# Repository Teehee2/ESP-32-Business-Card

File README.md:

# ESP-32-Business-Card
Personal Business Card with fully functional ESP-32 and NFC

Latest version V0.2

Friends with version V0.1: PLEASE TAKE NOTE!
DO NOT USE CLIP POINT USB 5V! IT WILL SHORT TO GROUND!

For DIY users:
V0.1 is flawed with mixed up tx/rx traces! Enamel wires need to be flown to use ESP32!
SW1 does not work with resistor R9, it is recommended to short the pads across R9.

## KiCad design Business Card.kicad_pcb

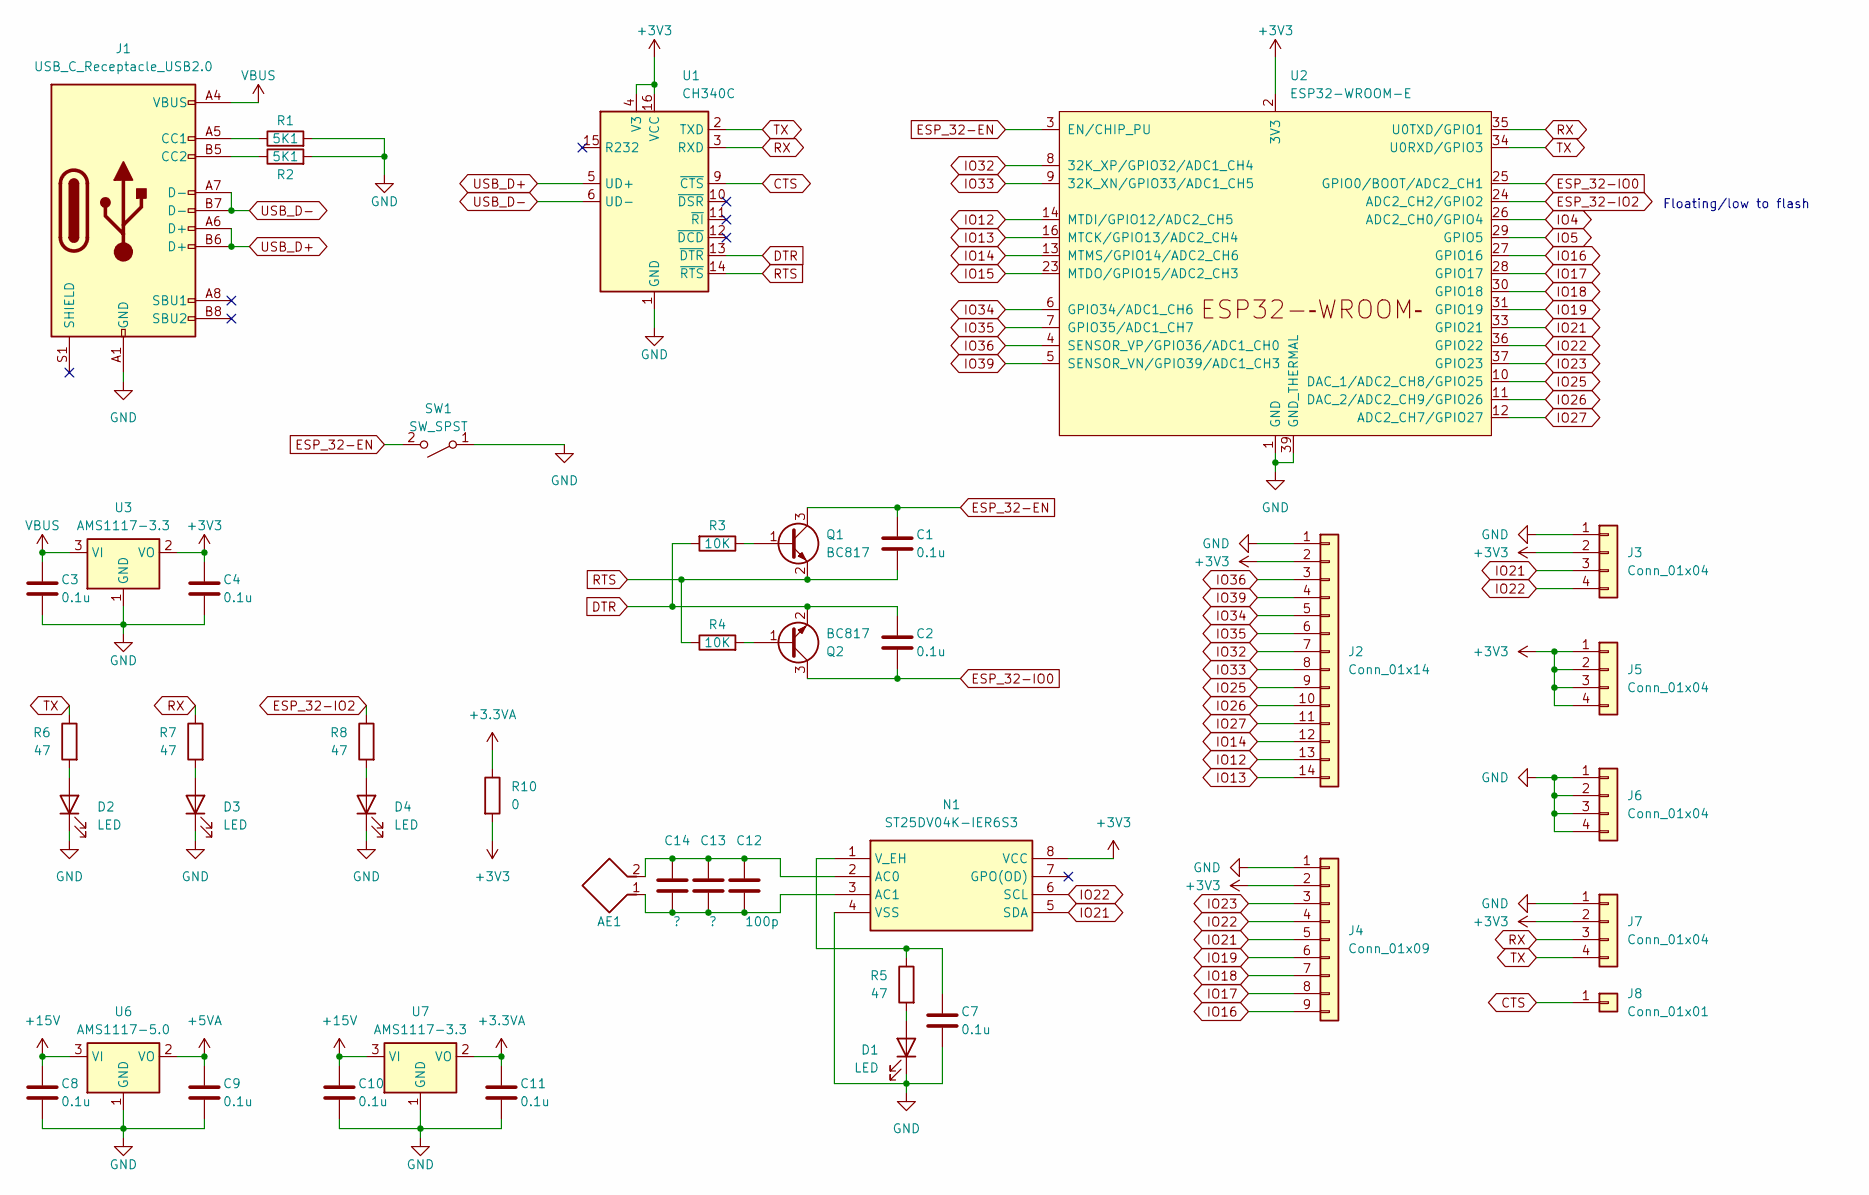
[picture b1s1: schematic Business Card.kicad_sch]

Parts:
AE1: NFC2
C1, C2, C3, C4, C7, C8, C9, C10, C11: 0.1u; C_0603_1608Metric
C12: 100p; C_0603_1608Metric
C13, C14: ?; C_0603_1608Metric
D1, D2, D3, D4: LED; LED_0603_1608Metric
J1: USB_C_Receptacle_USB2.0; USB_C_Receptacle_HRO_TYPE-C-31-M-12
J2: Conn_01x14; PinHeader_1x14_P2.54mm_Vertical_1_No_Silk
J3, J5, J6, J7: Conn_01x04; PinHeader_1x04_P2.54mm_Vertical_No_Silk
J4: Conn_01x09; PinHeader_1x09_P2.54mm_Vertical_No_Silk
J8: Conn_01x01; PinHeader_1x01_P2.54mm_Vertical_No_Silk
N1: ST25DV04K-IER6S3; SOIC-8-1EP_3.9x4.9mm_P1.27mm_EP2.41x3.3mm; Manufacturer_Part_Number ST25DV04K-IER6S3; Mouser Part Number 511-ST25DV04K-IER6S3
Q1, Q2: BC817; SOT-23
R1, R2: 5K1; R_0603_1608Metric
R3, R4: 10K; R_0603_1608Metric
R5, R6, R7, R8: 47; R_0603_1608Metric
R10: 0; R_0603_1608Metric
SW1: SW_SPST; SW_DIP_SPSTx01_Slide_Copal_CHS-01B_W7.62mm_P1.27mm
U1: CH340C; SOIC-16_3.9x9.9mm_P1.27mm
U2: ESP32-WROOM-E; ESP32-WROOM-32E
U3, U7: AMS1117-3.3; SOT-223-3_TabPin2
U6: AMS1117-5.0; SOT-223-3_TabPin2

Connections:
+3.3VA: C11.1, R10.1, U7.2 (VO)
+3V3: C4.1, J2.2, J3.2, J4.2, J5.1, J5.2, J5.3, J5.4, J7.2, N1.8 (VCC), R10.2, U1.4 (V3), U1.16 (VCC), U2.2 (3V3), U3.2 (VO)
+5VA: C9.1, U6.2 (VO)
+15V: C8.1, C10.1, U6.3 (VI), U7.3 (VI)
CTS: J8.1, U1.9 (~CTS)
DTR: C2.1, Q2.2 (E), R3.2, U1.13 (~DTR)
ESP_32-EN: C1.1, Q1.3 (C), SW1.2 (B), U2.3 (EN/CHIP_PU)
ESP_32-IO0: C2.2, Q2.3 (C), U2.25 (GPIO0/BOOT/ADC2_CH1)
ESP_32-IO2: R8.1, U2.24 (ADC2_CH2/GPIO2)
GND: C3.2, C4.2, C7.2, C8.2, C9.2, C10.2, C11.2, D1.1 (K), D2.1 (K), D3.1 (K), D4.1 (K), J1.A1 (GND), J1.A12 (GND), J1.B1 (GND), J1.B12 (GND), J2.1, J3.1, J4.1, J6.1, J6.2, J6.3, J6.4, J7.1, N1.4 (VSS), R1.2, R2.2, SW1.1 (A), U1.1 (GND), U2.1 (GND), U2.15 (GND), U2.38 (GND), U2.39 (GND_THERMAL), U3.1 (GND), U6.1 (GND), U7.1 (GND); also elsewhere on the board
IO4: U2.26 (ADC2_CH0/GPIO4)
IO5: U2.29 (GPIO5)
IO12: J2.13, U2.14 (MTDI/GPIO12/ADC2_CH5)
IO13: J2.14, U2.16 (MTCK/GPIO13/ADC2_CH4)
IO14: J2.12, U2.13 (MTMS/GPIO14/ADC2_CH6)
IO15: U2.23 (MTDO/GPIO15/ADC2_CH3)
IO16: J4.9, U2.27 (GPIO16)
IO17: J4.8, U2.28 (GPIO17)
IO18: J4.7, U2.30 (GPIO18)
IO19: J4.6, U2.31 (GPIO19)
IO21: J3.3, J4.5, N1.5 (SDA), U2.33 (GPIO21)
IO22: J3.4, J4.4, N1.6 (SCL), U2.36 (GPIO22)
IO23: J4.3, U2.37 (GPIO23)
IO25: J2.9, U2.10 (DAC_1/ADC2_CH8/GPIO25)
IO26: J2.10, U2.11 (DAC_2/ADC2_CH9/GPIO26)
IO27: J2.11, U2.12 (ADC2_CH7/GPIO27)
IO32: J2.7, U2.8 (32K_XP/GPIO32/ADC1_CH4)
IO33: J2.8, U2.9 (32K_XN/GPIO33/ADC1_CH5)
IO34: J2.5, U2.6 (GPIO34/ADC1_CH6)
IO35: J2.6, U2.7 (GPIO35/ADC1_CH7)
IO36: J2.3, U2.4 (SENSOR_VP/GPIO36/ADC1_CH0)
IO39: J2.4, U2.5 (SENSOR_VN/GPIO39/ADC1_CH3)
unnamed: D1.2 (A), R5.2
unnamed: D2.2 (A), R6.2
unnamed: D3.2 (A), R7.2
unnamed: D4.2 (A), R8.2
unnamed: J1.A5 (CC1), R1.1
unnamed: J1.B5 (CC2), R2.1
unnamed: AE1.2, C12.1, C13.1, C14.1, N1.2 (AC0)
unnamed: AE1.1, C12.2, C13.2, C14.2, N1.3 (AC1)
unnamed: C7.1, N1.1 (V_EH), R5.1
unnamed: Q1.1 (B), R3.1
unnamed: Q2.1 (B), R4.2
RTS: C1.2, Q1.2 (E), R4.1, U1.14 (~RTS)
RX: J7.3, R7.1, U1.3 (RXD), U2.35 (U0TXD/GPIO1)
TX: J7.4, R6.1, U1.2 (TXD), U2.34 (U0RXD/GPIO3)
USB_D+: J1.A6 (D+), J1.B6 (D+), U1.5 (UD+)
USB_D-: J1.A7 (D-), J1.B7 (D-), U1.6 (UD-)
VBUS: C3.1, J1.A4 (VBUS), J1.A9 (VBUS), J1.B4 (VBUS), J1.B9 (VBUS), U3.3 (VI)

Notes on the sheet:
Floating/low to flash

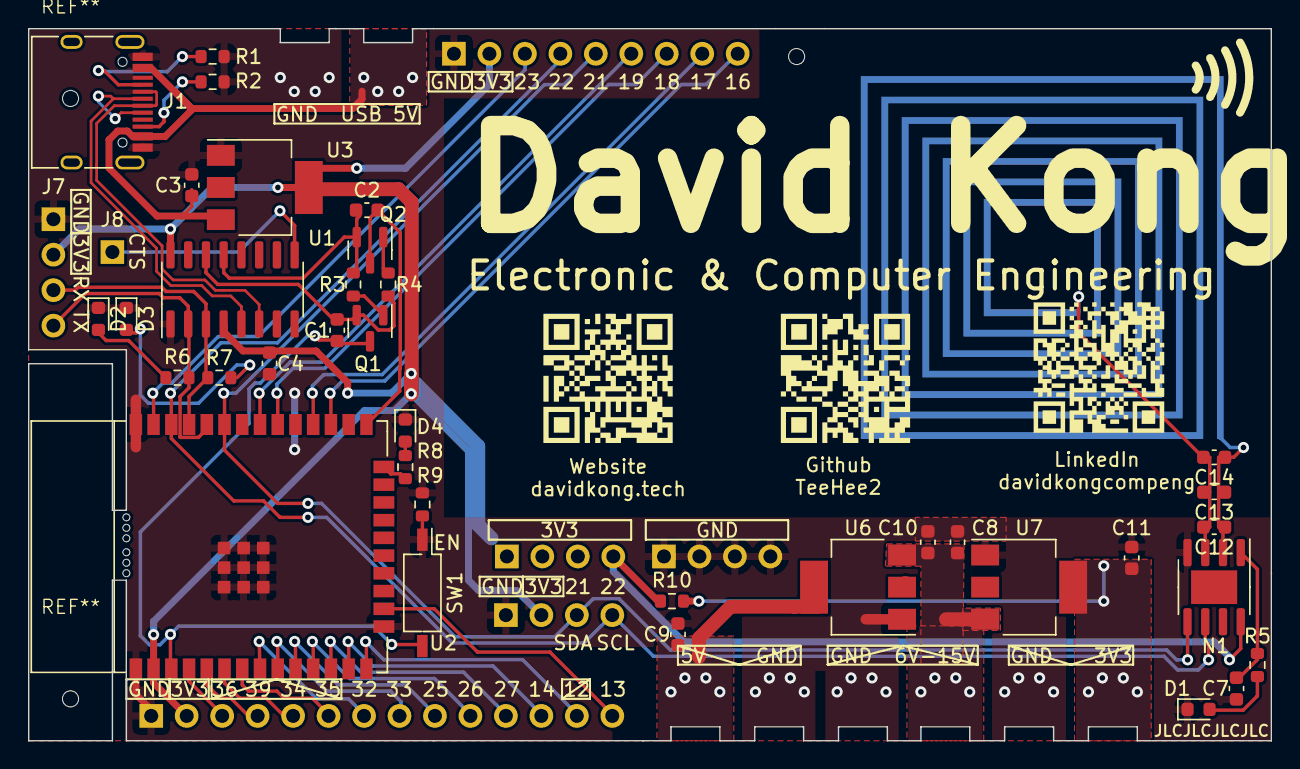
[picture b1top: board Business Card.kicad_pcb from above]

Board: 2 copper layers, 89.0 x 51.0 mm, 46 parts (1 on the bottom side), 46 nets.

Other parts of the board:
R9: 10K; R_0603_1608Metric
mouse-bite-2mm-slot, mouse-bite-2mm-slot#2: VAL**; mouse-bite-2mm-slot_1

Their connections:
GND: R9.1; also elsewhere on the board
